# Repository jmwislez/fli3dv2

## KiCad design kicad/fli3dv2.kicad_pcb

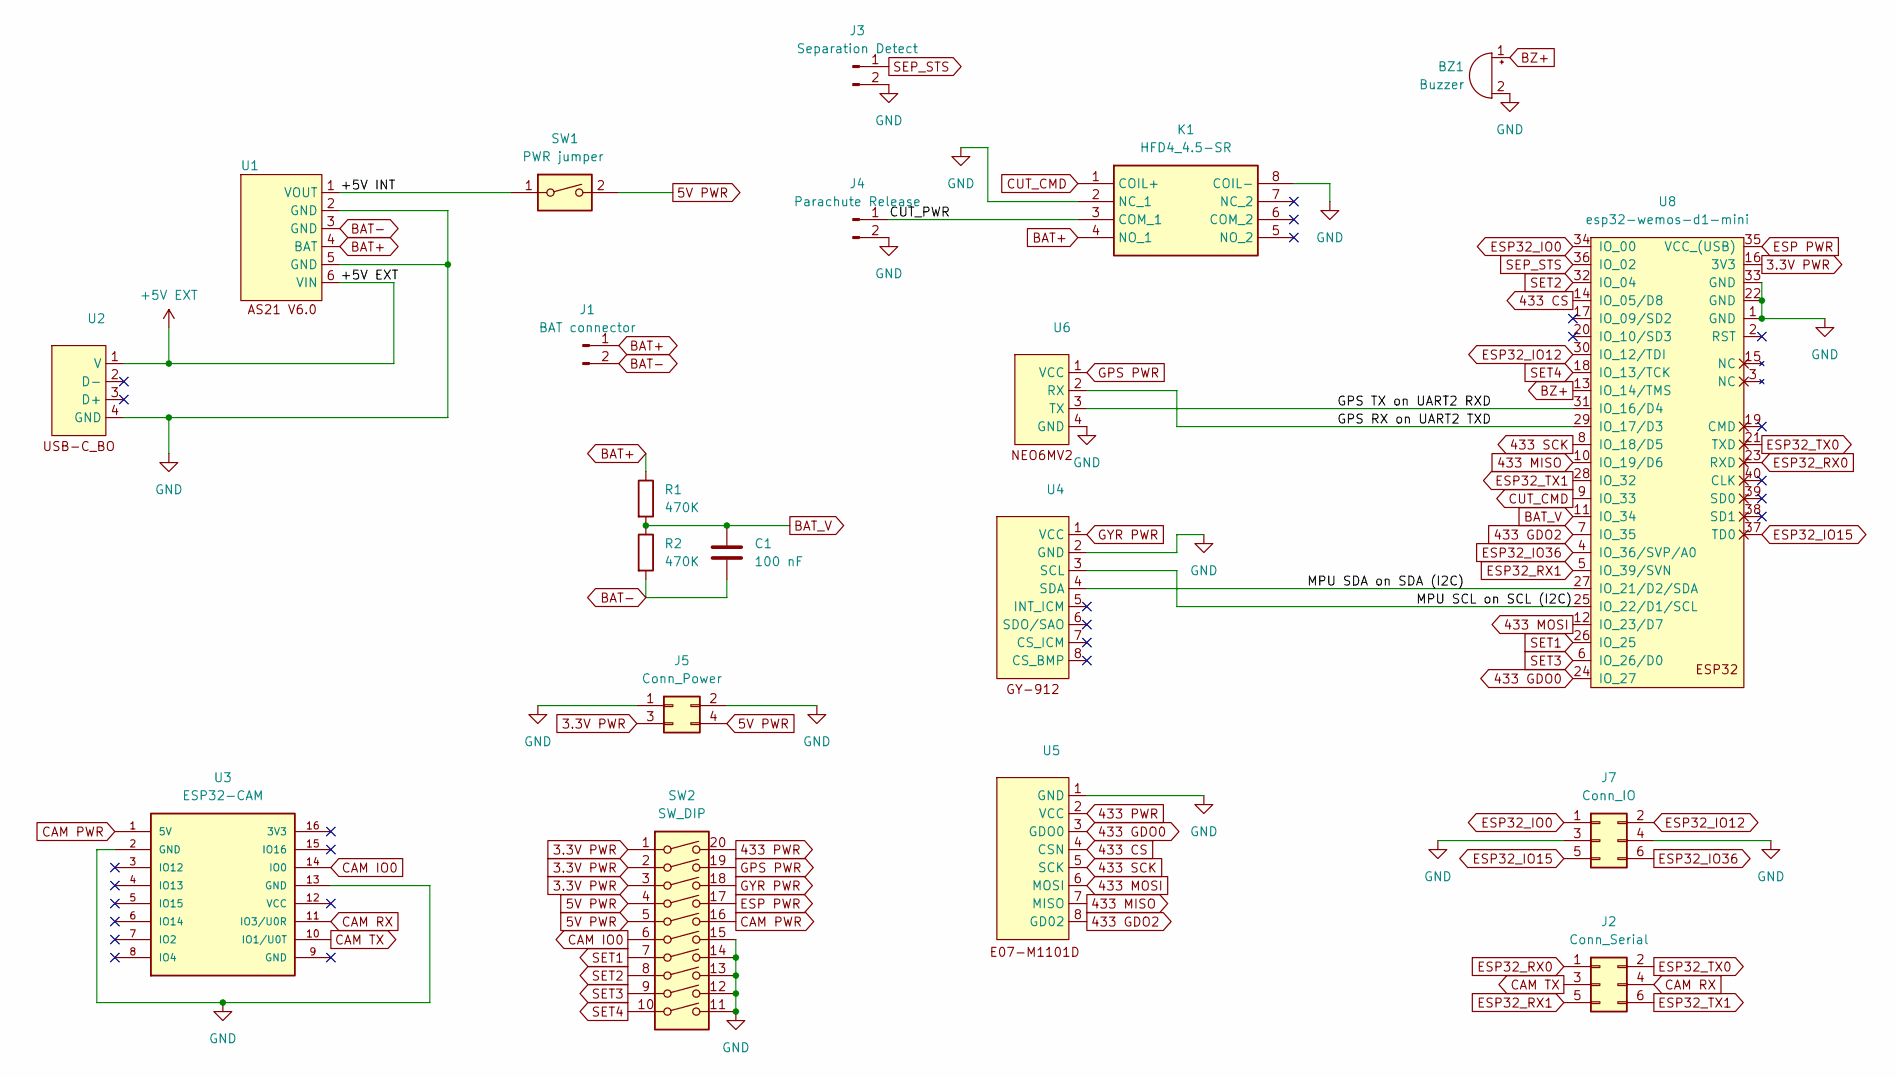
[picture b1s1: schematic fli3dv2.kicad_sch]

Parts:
BZ1: Buzzer; mini buzzer
C1: 100 nF; C_Disc_D3.0mm_W2.0mm_P2.50mm
J1: BAT connector; XHP_1x02_P2.54mm
J2: Conn_Serial; PinHeader_2x03_P2.54mm_Vertical
J3: Separation Detect; XHP_1x02_P2.54mm
J4: Parachute Release; XHP_1x02_P2.54mm
J5: Conn_Power; PinSocket_2x02_P2.54mm_Vertical
J7: Conn_IO; PinHeader_2x03_P2.54mm_Vertical
K1: HFD4_4.5-SR; HFD445SR; Manufacturer_Part_Number HFD4/4.5-SR
R1, R2: 470K; R_Axial_DIN0207_L6.3mm_D2.5mm_P10.16mm_Horizontal
SW1: PWR jumper; PinHeader_1x02_P2.54mm_Horizontal
SW2: SW_DIP; SW_DIP_SPSTx10_Slide_KingTek_DSHP10TS_W7.62mm_P1.27mm
U1: AS21
U2: USB-C connector
U3: ESP32-CAM; Ai-Thinker_ESP32-CAM
U4: GY-912
U5: E07-M1101D
U6: NEO6MV2 (4 pins)_flipped
U8: esp32-wemos-d1-mini

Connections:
3.3V PWR: J5.3, SW2.1, SW2.2, SW2.3, U8.16 (3V3)
5V PWR: J5.4, SW1.2, SW2.4, SW2.5
433 CS: U5.4 (CSN), U8.14 (IO_05/D8)
433 GDO0: U5.3 (GDO0), U8.24 (IO_27)
433 GDO2: U5.8 (GD02), U8.7 (IO_35)
433 MISO: U5.7 (MISO), U8.10 (IO_19/D6)
433 MOSI: U5.6 (MOSI), U8.12 (IO_23/D7)
433 PWR: SW2.20, U5.2 (VCC)
433 SCK: U5.5 (SCK), U8.8 (IO_18/D5)
+5V EXT: U1.6 (VIN), U2.1 (V)
/+5V INT: SW1.1, U1.1 (VOUT)
/CUT_PWR: J4.1, K1.3 (COM_1)
/GPS RX on UART2 TXD: U6.2 (RX), U8.29 (IO_17/D3)
/GPS TX on UART2 RXD: U6.3 (TX), U8.31 (IO_16/D4)
/MPU SCL on SCL (I2C): U4.3 (SCL), U8.25 (IO_22/D1/SCL)
/MPU SDA on SDA (I2C): U4.4 (SDA), U8.27 (IO_21/D2/SDA)
BAT+: J1.1, K1.4 (NO_1), R1.1, U1.4 (BAT)
BAT-: C1.2, J1.2, R2.2, U1.3 (GND)
BAT_V: C1.1, R1.2, R2.1, U8.11 (IO_34)
BZ+: BZ1.1 (+), U8.13 (IO_14/TMS)
CAM IO0: SW2.6, U3.14 (IO0)
CAM PWR: SW2.16, U3.1 (5V)
CAM RX: J2.4, U3.11 (IO3/U0R)
CAM TX: J2.3, U3.10 (IO1/U0T)
CUT_CMD: K1.1 (COIL+), U8.9 (IO_33)
ESP32_IO0: J7.1, U8.34 (IO_00)
ESP32_IO12: J7.2, U8.30 (IO_12/TDI)
ESP32_IO15: J7.5, U8.37 (TD0)
ESP32_IO36: J7.6, U8.4 (IO_36/SVP/A0)
ESP32_RX0: J2.1, U8.23 (RXD)
ESP32_RX1: J2.5, U8.5 (IO_39/SVN)
ESP32_TX0: J2.2, U8.21 (TXD)
ESP32_TX1: J2.6, U8.28 (IO_32)
ESP PWR: SW2.17, U8.35 (VCC_(USB))
GND: BZ1.2 (-), J3.2, J4.2, J5.1, J5.2, J7.3, J7.4, K1.2 (NC_1), K1.8 (COIL-), SW2.11, SW2.12, SW2.13, SW2.14, SW2.15, U1.2 (GND), U1.5 (GND), U2.4 (GND), U3.2 (GND), U3.13 (GND), U4.2 (GND), U5.1 (GND), U6.4 (GND), U8.1 (GND), U8.22 (GND), U8.33 (GND)
GPS PWR: SW2.19, U6.1 (VCC)
GYR PWR: SW2.18, U4.1 (VCC)
SEP_STS: J3.1, U8.36 (IO_02)
SET1: SW2.7, U8.26 (IO_25)
SET2: SW2.8, U8.32 (IO_04)
SET3: SW2.9, U8.6 (IO_26/D0)
SET4: SW2.10, U8.18 (IO_13/TCK)

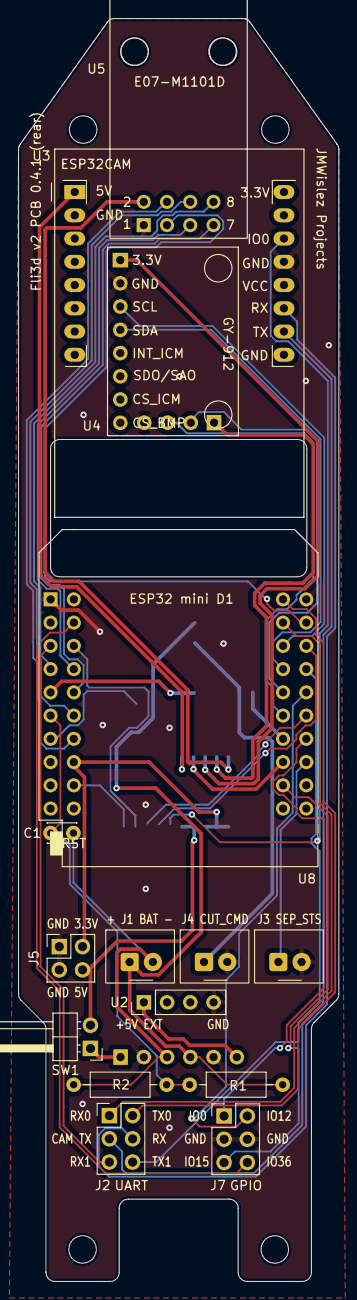
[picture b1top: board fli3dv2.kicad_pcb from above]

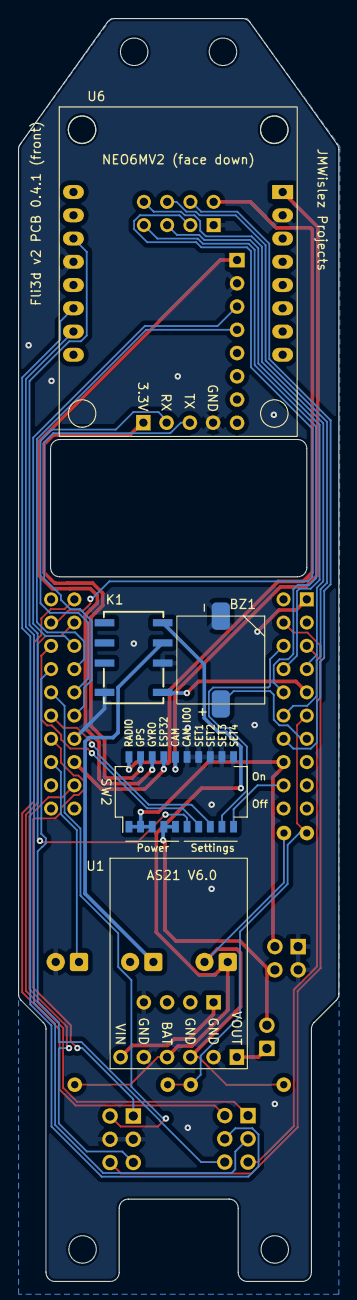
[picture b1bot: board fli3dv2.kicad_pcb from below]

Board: 2 copper layers, 35.0 x 138.0 mm, 20 parts (5 on the bottom side), 42 nets.

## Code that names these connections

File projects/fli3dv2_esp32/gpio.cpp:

/*
 * Fli3d - GPIO functionality
 *
 * SET1: buzzer on/off (ON for flight)
 * SET2: FS flushing on/off (OFF for flight)
 * SET3: FS writable (on) / read only (off) (ON for flight)
 * SET4: camera acquisition on/off (ON for flight)
 * 
 */

 #include <Arduino.h>
 #include <fli3dv2.h>
 #include "fli3dv2_esp32.h"
 
void setup_gpio()
{
    pinMode(SET1_PIN, INPUT_PULLUP);
    pinMode(SET2_PIN, INPUT_PULLUP);
    pinMode(SET3_PIN, INPUT_PULLUP);
    pinMode(SET4_PIN, INPUT_PULLUP);
    cfg_this->dip_set1 = !digitalRead (SET1_PIN);
    cfg_this->dip_set2 = !digitalRead (SET2_PIN);
    cfg_this->dip_set3 = !digitalRead (SET3_PIN);
    cfg_this->dip_set4 = !digitalRead (SET4_PIN);
    sprintf (buffer, "DIP switch settings acquired (1:%d 2:%d 3:%d 4:%d)", cfg_this->dip_set1, cfg_this->dip_set2, cfg_this->dip_set3, cfg_this->dip_set4);
    publish_event (STS_THIS, SS_THIS, EVENT_INIT, buffer);

    // SET1
    cfg_this->buzzer_enable=cfg_this->dip_set1;
    if (cfg_this->dip_set1) {
        sprintf (buffer, "Enabled buzzer based on DIP switch 1 (on)");
    }
    else {
        sprintf (buffer, "Disabled buzzer based on DIP switch 1 (off)");
    }
    publish_event (STS_THIS, SS_THIS, EVENT_INIT, buffer);

    // SET2
    cfg_this->flush_fs_enable=cfg_this->dip_set2;
    if (cfg_this->dip_set2) {
        sprintf (buffer, "Enabled LittleFS flushing at boot based on DIP switch 2 (on)");
    }
    else {
        sprintf (buffer, "Disabled LittleFS flushing at boot based on DIP switch 2 (off)");
    }
    publish_event (STS_THIS, SS_THIS, EVENT_INIT, buffer);

    // SET3
    cfg_this->write_fs_enable=cfg_this->dip_set3; // TODO: IMPLEMENT!
    if (cfg_this->dip_set3) {
        sprintf (buffer, "Made LittleFS writable based on DIP switch 3 (on)");
    }
    else {
        sprintf (buffer, "Made LittleFS read-only based on DIP switch 3 (off)");
    }
    publish_event (STS_THIS, SS_THIS, EVENT_INIT, buffer);
    
    // SET4
    cfg_this->force_esp32cam_nominal=cfg_this->dip_set4;
    if (cfg_this->dip_set4) {
        sprintf (buffer, "Start ESP32 and ESP32CAM in Nominal mode based on DIP switch 4 (on)");
        cfg_this->target_opsmode = MODE_NOMINAL;
    }
    else {
        sprintf (buffer, "Start ESP32 and ESP32CAM in default mode based on DIP switch 4 (off)");
    }
    publish_event (STS_THIS, SS_THIS, EVENT_INIT, buffer);

    // Other SET uses

    /* if (cfg_this->dip_set3) {
        sprintf (buffer, "Using boot configuration stored in EEPROM based on DIP switch 3 (on)");
    }
    else {
        sprintf (buffer, "Skipping stored boot configuration based on DIP switch 3 (off)");
        cfg_this->cfg_boot.boot_bank=255; // force to skip stored boot configuration
    }
    publish_event (STS_THIS, SS_THIS, EVENT_INIT, buffer); */

}
